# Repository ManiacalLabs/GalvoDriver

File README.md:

# GalvoDriver
Galvanometer Controller, DAC and Audio In

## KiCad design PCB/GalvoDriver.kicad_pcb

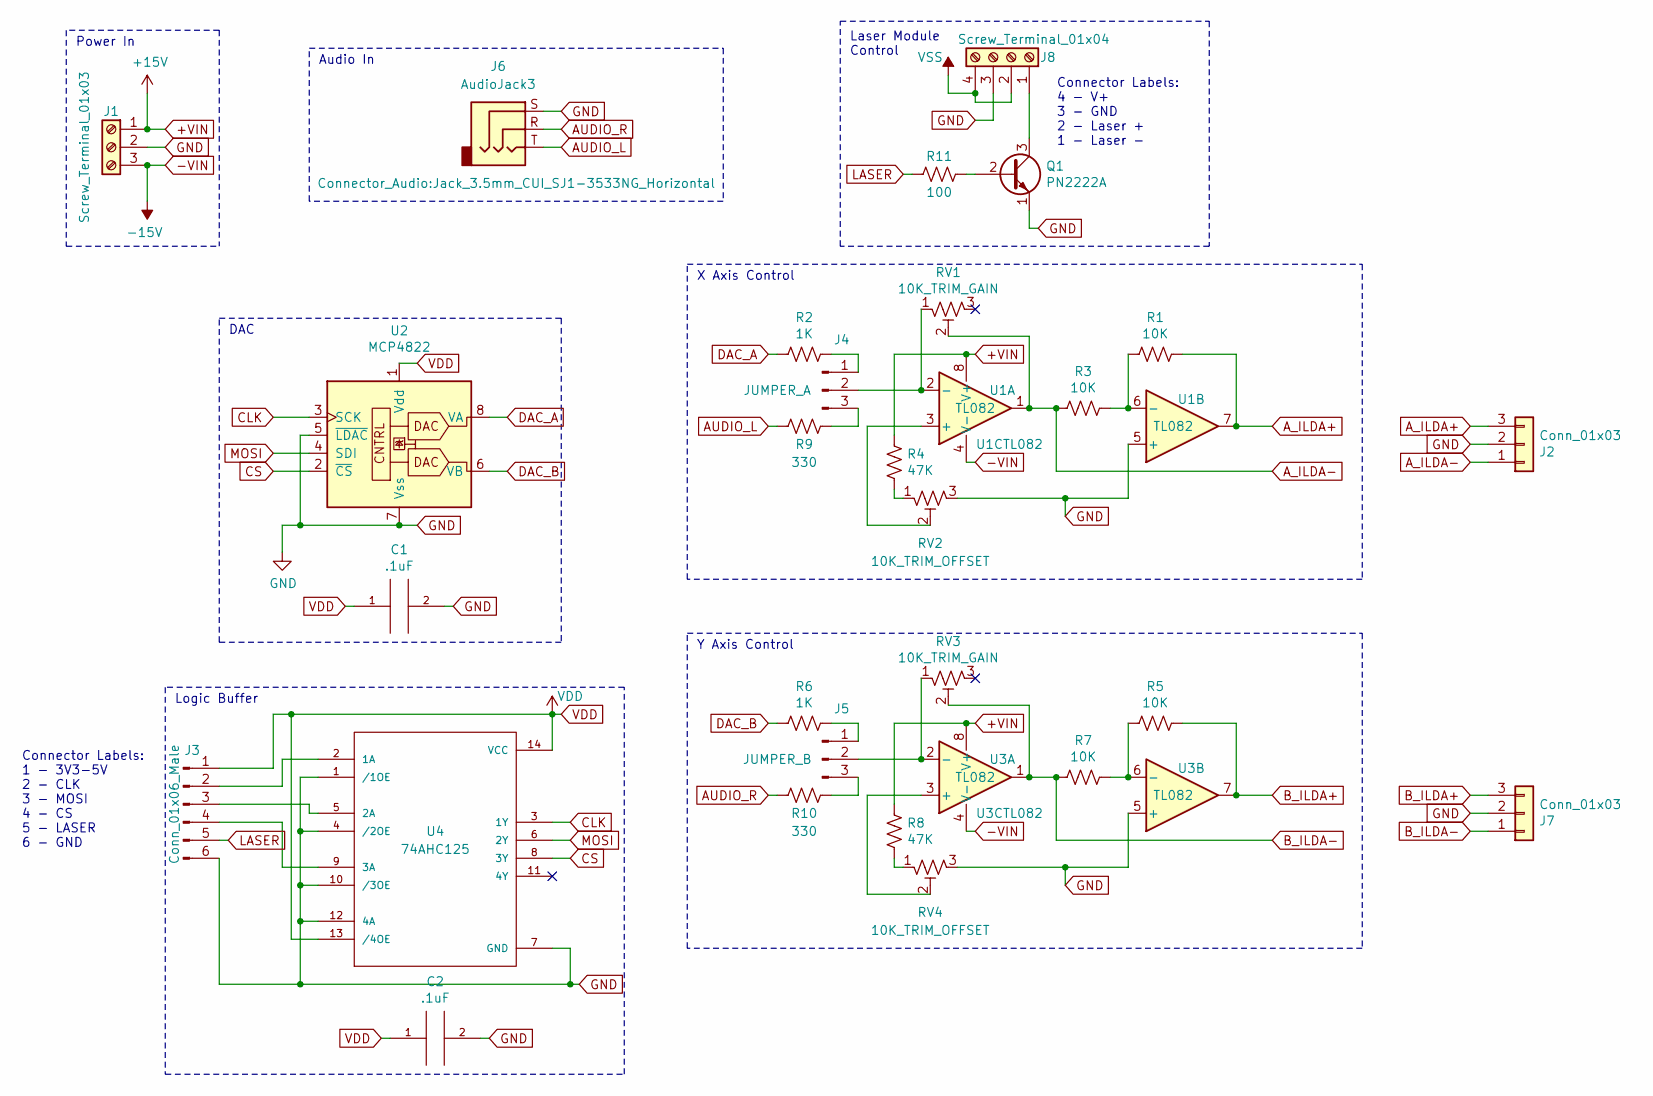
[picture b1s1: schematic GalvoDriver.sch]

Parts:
C1, C2: .1uF; C_Disc_D5.0mm_W2.5mm_P2.50mm
J1: Screw_Terminal_01x03; TerminalBlock_Phoenix_MKDS1.5-3pol
J2, J7: Conn_01x03; JST_XH_B03B-XH-A_03x2.50mm_Straight
J3: Conn_01x06_Male; Pin_Header_Straight_1x06_Pitch2.54mm
J4: JUMPER_A; Pin_Header_Straight_1x03_Pitch2.54mm
J5: JUMPER_B; Pin_Header_Straight_1x03_Pitch2.54mm
J6: AudioJack3; Jack_3.5mm_CUI_SJ1-3533NG_Horizontal
J8: Screw_Terminal_01x04; TerminalBlock_Phoenix_MKDS1.5-4pol
Q1: PN2222A; TO-92_Inline_Wide
R1, R3, R5, R7: 10K; R_Axial_DIN0207_L6.3mm_D2.5mm_P10.16mm_Horizontal
R2, R6: 1K; R_Axial_DIN0207_L6.3mm_D2.5mm_P10.16mm_Horizontal
R4, R8: 47K; R_Axial_DIN0207_L6.3mm_D2.5mm_P10.16mm_Horizontal
R9, R10: 330; R_Axial_DIN0207_L6.3mm_D2.5mm_P10.16mm_Horizontal
R11: 100; R_Axial_DIN0207_L6.3mm_D2.5mm_P10.16mm_Horizontal
RV1, RV3: 10K_TRIM_GAIN; Potentiometer_Trimmer_Bourns_3296W
RV2, RV4: 10K_TRIM_OFFSET; Potentiometer_Trimmer_Bourns_3296W
U1, U3: TL082; DIP-8_W7.62mm_Socket
U2: MCP4822; DIP-8_W7.62mm_Socket
U4: 74AHC125; DIP-14_W7.62mm_Socket

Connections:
+VIN: J1.1, R4.2, R8.2, U1.8 (V+), U3.8 (V+)
-VIN: J1.3, U1.4 (V-), U3.4 (V-)
AUDIO_L: J6.T, R9.2
AUDIO_R: J6.R, R10.2
A_ILDA+: J2.3, R1.1, U1.7
A_ILDA-: J2.1, R3.2, RV1.2, U1.1
B_ILDA+: J7.3, R5.1, U3.7
B_ILDA-: J7.1, R7.2, RV3.2, U3.1
CLK: U2.3 (SCK), U4.3 (1Y)
CS: U2.2 (~CS), U4.8 (3Y)
DAC_A: R2.2, U2.8 (VA)
DAC_B: R6.2, U2.6 (VB)
GND: C1.2, C2.2, J1.2, J2.2, J3.6, J6.S, J7.2, J8.3, Q1.1 (E), RV2.3, RV4.3, U1.5 (+), U2.5 (~LDAC), U2.7 (Vss), U3.5 (+), U4.1 (/1OE), U4.4 (/2OE), U4.7 (GND), U4.10 (/3OE), U4.12 (4A)
LASER: J3.5, R11.2
MOSI: U2.4 (SDI), U4.6 (2Y)
unnamed: J3.2, U4.2 (1A)
unnamed: J3.3, U4.5 (2A)
unnamed: J3.4, U4.9 (3A)
unnamed: J4.1, R2.1
unnamed: J4.2, RV1.1, U1.2 (-)
unnamed: J4.3, R9.1
unnamed: J5.1, R6.1
unnamed: J5.2, RV3.1, U3.2 (-)
unnamed: J5.3, R10.1
unnamed: J8.1, Q1.3 (C)
unnamed: Q1.2 (B), R11.1
unnamed: R1.2, R3.1, U1.6 (-)
unnamed: R4.1, RV2.1
unnamed: R5.2, R7.1, U3.6 (-)
unnamed: R8.1, RV4.1
unnamed: RV2.2, U1.3 (+)
unnamed: RV4.2, U3.3 (+)
VDD: C1.1, C2.1, J3.1, U2.1 (Vdd), U4.13 (/4OE), U4.14 (VCC)
VSS: J8.2, J8.4

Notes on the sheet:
Connector Labels: 1 - 3V3-5V 2 - CLK 3 - MOSI 4 - CS 5 - LASER 6 - GND
Y Axis Control
X Axis Control
Connector Labels: 4 - V+ 3 - GND 2 - Laser + 1 - Laser -
Laser Module Control
Power In
DAC
Audio In
Logic Buffer

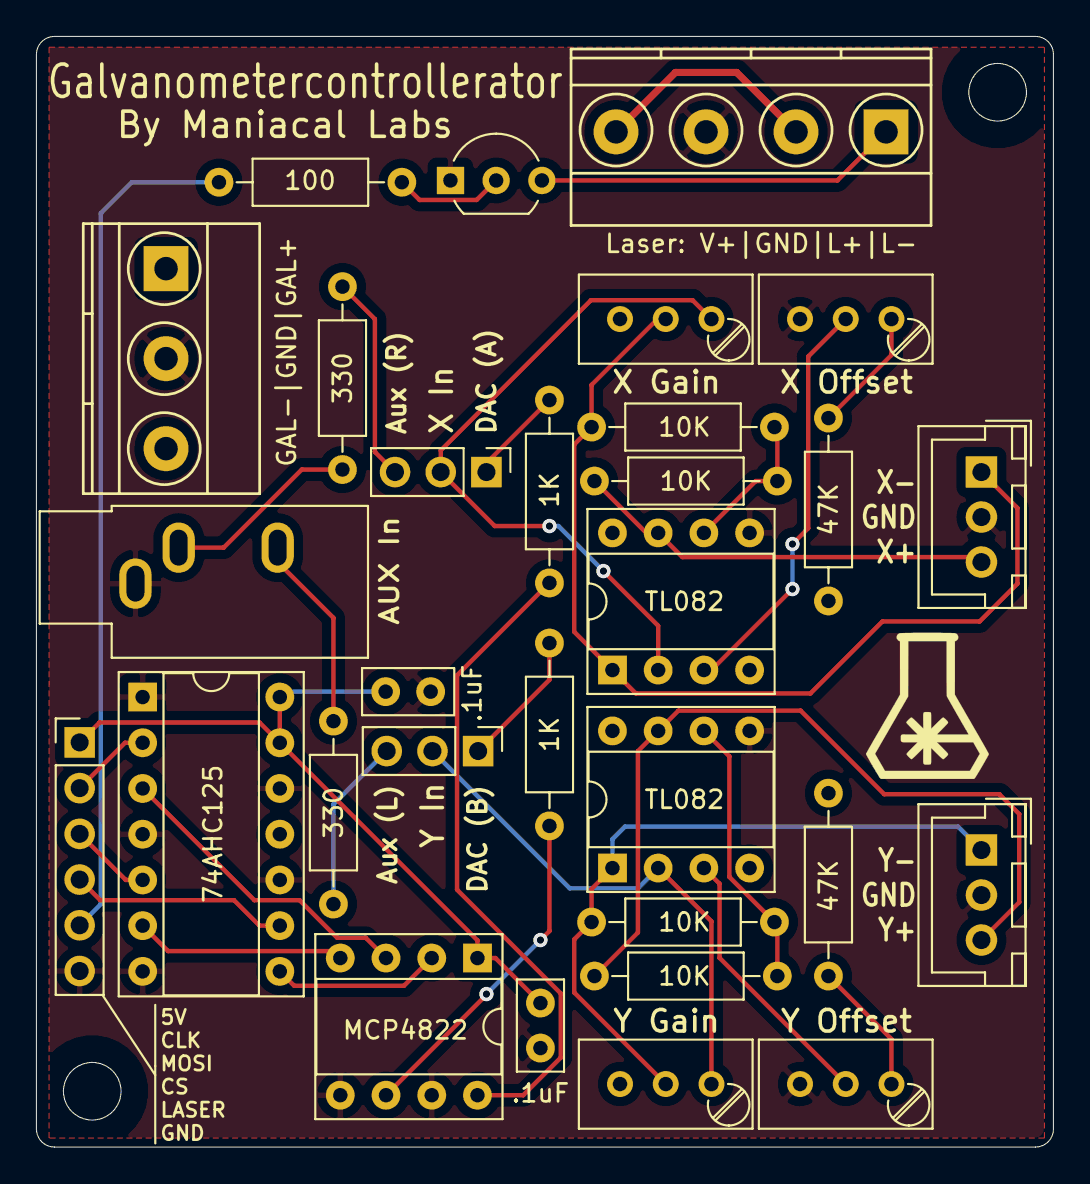
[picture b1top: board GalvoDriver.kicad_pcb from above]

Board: 4 copper layers, 56.5 x 61.7 mm, 30 parts (0 on the bottom side), 34 nets.

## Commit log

2020-06-28 Create Repo, README commit
2020-06-28 KiCAD Project commit
2020-06-28 Moved to PCB dir
2020-07-07 Added Laser Module Control + terminal
2020-07-07 Added terminal labels, exported gerbers for fab.
2020-07-14 Changed decoupling cap value to 0.1uF
2020-07-27 WIP Control Code
2020-07-28 starting on custom shapes
2020-08-01 Working on cleanup
2020-08-02 code cleanup
2020-08-02 Tweaks
2020-08-19 Starting work on PCB changes for v1.1
2020-08-19 Level shifter, thrm. relief, xistor pad, audio jack move
2020-08-19 Fixing Aux In and C2 silk
2020-08-22 misc code tweaks
2020-09-03 Generated gerber files, uploaded v2 to board fab.
2020-09-12 Functional swap buffers
2020-10-02 Added CS connection to header, buffer, DAC input
2020-10-03 Flipped ILDA connector wiring and silkscreen labels
